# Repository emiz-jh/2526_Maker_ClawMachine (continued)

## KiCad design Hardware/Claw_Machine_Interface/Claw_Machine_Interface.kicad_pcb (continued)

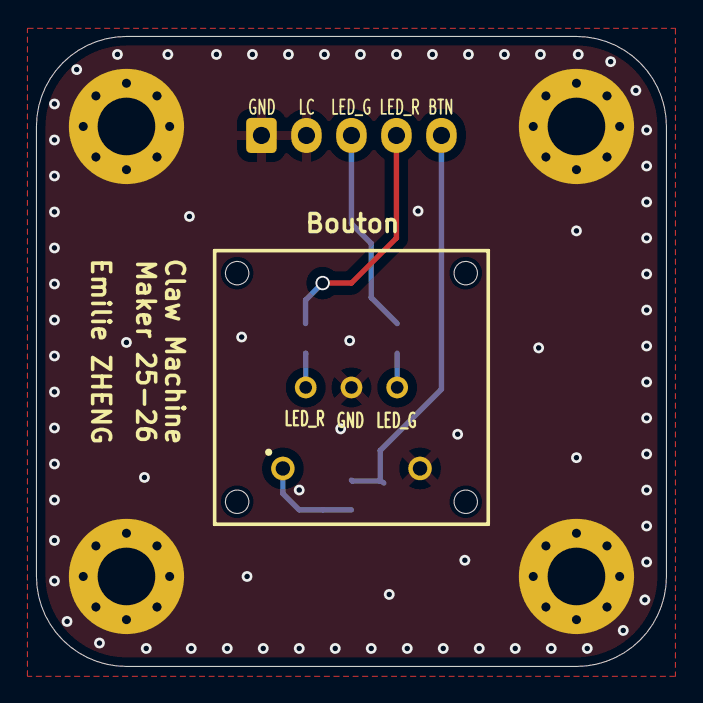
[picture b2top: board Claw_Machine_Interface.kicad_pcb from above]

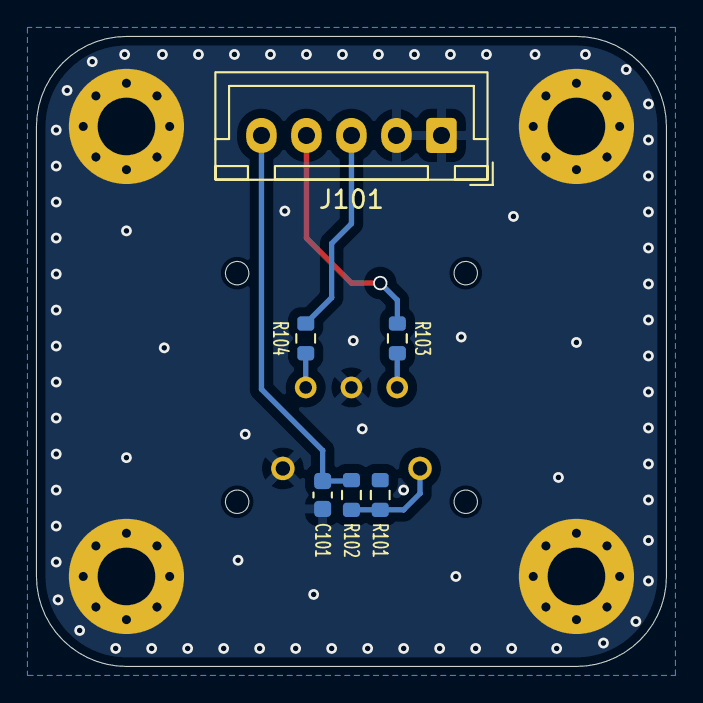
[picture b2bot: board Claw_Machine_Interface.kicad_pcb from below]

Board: 2 copper layers, 35.0 x 35.0 mm, 11 parts (6 on the bottom side), 7 nets.

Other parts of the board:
Bouton: 465RG11172501_bis

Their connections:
/LED_G: Bouton.6; also elsewhere on the board
/LED_R: Bouton.4; also elsewhere on the board
GND: Bouton.2, Bouton.5 (LC); also elsewhere on the board
unnamed 7: Bouton.1; also elsewhere on the board

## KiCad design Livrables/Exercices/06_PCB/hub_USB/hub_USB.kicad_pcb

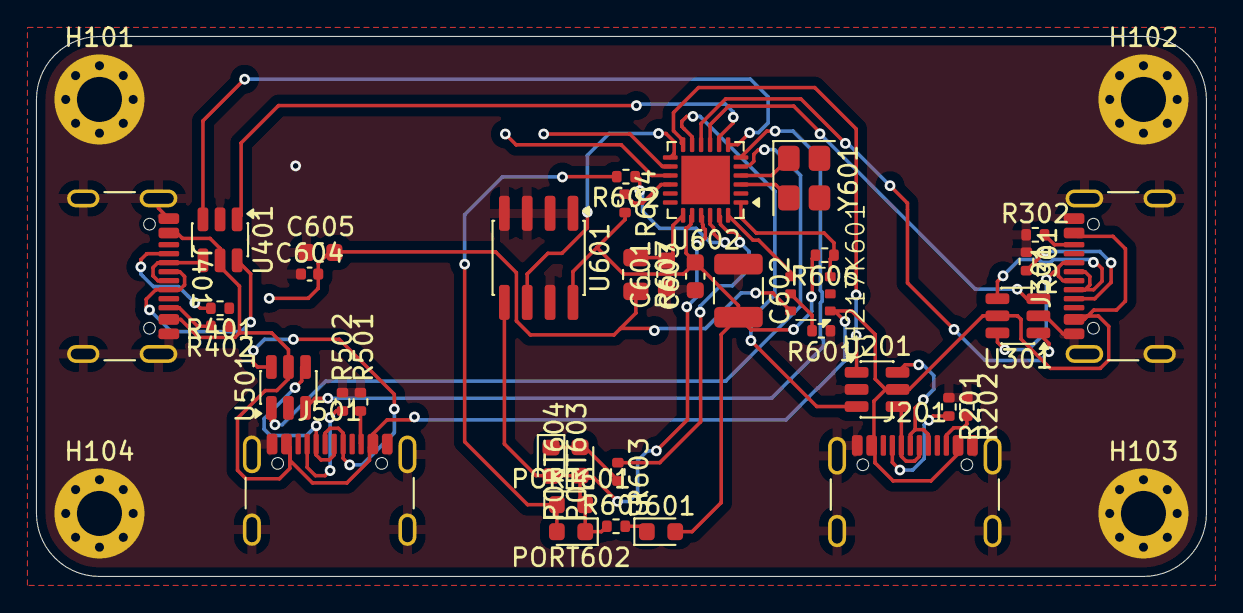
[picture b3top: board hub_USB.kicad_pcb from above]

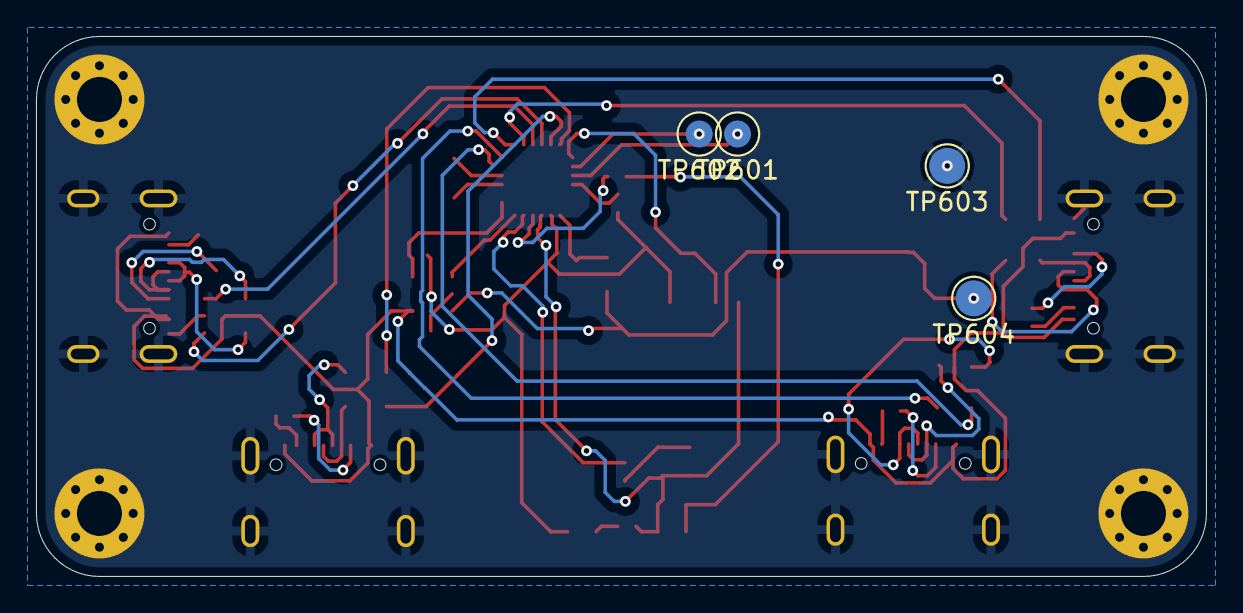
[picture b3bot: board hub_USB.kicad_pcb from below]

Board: 4 copper layers, 65.0 x 30.0 mm, 45 parts (4 on the bottom side), 44 nets.

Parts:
C601, C605: 1uF; C_0603_1608Metric
C602: 10uF; C_1210_3225Metric
C603: 0.1uF; C_0603_1608Metric
C604: 470uF; C_0402_1005Metric
CH217K601: CH217DS1
D601: ACTIVE; LED_0603_1608Metric
H101, H102, H103, H104: MountingHole_Pad; MountingHole_2.5mm_Pad_Via
J201, J301, J401, J501: USB_C_Receptacle_USB2.0_16P; USB_C_Receptacle_GCT_USB4105-xx-A_16P_TopMnt_Horizontal
PORT601, PORT602, PORT603, PORT604: RED_LED; LED_0603_1608Metric
R201, R202, R301, R302, R401, R402, R501, R502: 5.1k; R_0402_1005Metric
R601: 56K; R_0402_1005Metric
R602, R603: 220; R_0402_1005Metric
R604: NC(4K7); R_0402_1005Metric
R605: 470; R_0402_1005Metric
R606: NC(56K); R_0402_1005Metric
R607: 0; Fuse_0805_2012Metric
TP601, TP602, TP603: TestPoint; TestPoint_Pad_D2.0mm
TP604: Alim; TestPoint_Pad_D2.0mm
U201, U301, U401, U501: USBLC6-2SC6; SOT-23-6
U601: 24C02Cx-x-SN; SOIC-8_3.9x4.9mm_P1.27mm
U602: CH334F; QFN-24-1EP_4x4mm_P0.5mm_EP2.7x2.7mm
Y601: 12MHz; Crystal_SMD_3225-4Pin_3.2x2.5mm

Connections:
+3V3: C602.2, C603.2, D601.2 (A), R604.2, R606.2, U601.8 (VCC), U602.20 (VDD33_{LDO})
+5V: C604.2, C605.2, CH217K601.6 (VIN), R607.2, TP604.1
/USB1/D+: J201.A6 (D+), J201.B6 (D+), U201.6 (I/O1)
/USB1/D-: J201.A7 (D-), J201.B7 (D-), U201.4 (I/O2)
/USB1/USB_DM: U201.3 (I/O2), U602.11 (DM1-)
/USB1/USB_DP: U201.1 (I/O1), U602.12 (DP1+)
/USB1/V_USB: CH217K601.1 (VOUT), J201.A4 (VBUS), J201.A9 (VBUS), J201.B4 (VBUS), J201.B9 (VBUS), J301.A4 (VBUS), J301.A9 (VBUS), J301.B4 (VBUS), J301.B9 (VBUS), J401.A4 (VBUS), J401.A9 (VBUS), J401.B4 (VBUS), J401.B9 (VBUS), J501.A4 (VBUS), J501.A9 (VBUS), J501.B4 (VBUS), J501.B9 (VBUS), U201.5 (VBUS), U301.5 (VBUS), U401.5 (VBUS), U501.5 (VBUS)
/USB2/D+: J301.A6 (D+), J301.B6 (D+), U301.6 (I/O1)
/USB2/D-: J301.A7 (D-), J301.B7 (D-), U301.4 (I/O2)
/USB2/USB_DM: U301.3 (I/O2), U602.9 (DM2-)
/USB2/USB_DP: U301.1 (I/O1), U602.10 (DP2+)
/USB3/D+: J401.A6 (D+), J401.B6 (D+), U401.6 (I/O1)
/USB3/D-: J401.A7 (D-), J401.B7 (D-), U401.4 (I/O2)
/USB3/USB_DM: U401.3 (I/O2), U602.7 (DM3-)
/USB3/USB_DP: U401.1 (I/O1), U602.8 (DP3+)
/USB4/D+: J501.A6 (D+), J501.B6 (D+), U501.6 (I/O1)
/USB4/D-: J501.A7 (D-), J501.B7 (D-), U501.4 (I/O2)
/USB4/USB_DM: U501.3 (I/O2), U602.6 (DP4+)
/USB4/USB_DP: U501.1 (I/O1), U602.5 (DM4-)
/USB_hub_controller/OVCUR#: CH217K601.3 (FLAG#), R606.1, U602.1 (~OVCUR)
/USB_hub_controller/PLED1: R602.1, U602.22 (LED1)
/USB_hub_controller/PLED2: R603.1, U602.23 (LED2)
/USB_hub_controller/PLED3: U601.6 (SCL), U602.13 (LED3/SCL)
/USB_hub_controller/PLED4: PORT601.2 (A), PORT602.1 (K), PORT603.2 (A), PORT604.1 (K), R605.1, U601.5 (SDA), U602.21 (LED4/SDA)
/USB_hub_controller/PW REN#: CH217K601.4 (EN#), U602.24 (~PWREN)
/USB_hub_controller/RESET#: R604.1, U602.16 (~RESET/CDP)
/USB_hub_controller/XI: U602.4 (XI), Y601.1
/USB_hub_controller/XO: U602.3 (XO), Y601.2
GND: C601.1, C602.1, C603.1, C604.1, C605.1, CH217K601.2 (GND), H101.1, H102.1, H103.1, H104.1, J201.A1 (GND), J201.A12 (GND), J201.B1 (GND), J201.B12 (GND), J201.S1 (SHIELD), J301.A1 (GND), J301.A12 (GND), J301.B1 (GND), J301.B12 (GND), J301.S1 (SHIELD), J401.A1 (GND), J401.A12 (GND), J401.B1 (GND), J401.B12 (GND), J401.S1 (SHIELD), J501.A1 (GND), J501.A12 (GND), J501.B1 (GND), J501.B12 (GND), J501.S1 (SHIELD), R201.1, R202.1, R301.1, R302.1, R401.1, R402.1, R501.1, R502.1, R601.1, TP603.1, U201.2 (GND), U301.2 (GND), U401.2 (GND), U501.2 (GND), U601.1 (A0), U601.2 (A1), U601.3 (A2), U601.4 (GND), U601.7 (WP), U602.25 (GND)
unnamed: CH217K601.5 (ISET), R601.2
unnamed: D601.1 (K), R605.2
unnamed: J201.A5 (CC1), R201.2
unnamed: J201.B5 (CC2), R202.2
unnamed: J301.A5 (CC1), R301.2
unnamed: J301.B5 (CC2), R302.2
unnamed: J401.A5 (CC1), R401.2
unnamed: J401.B5 (CC2), R402.2
unnamed: J501.A5 (CC1), R501.2
unnamed: J501.B5 (CC2), R502.2
unnamed: PORT601.1 (K), PORT602.2 (A), R602.2
unnamed: PORT603.1 (K), PORT604.2 (A), R603.2
unnamed: TP602.1, U602.14 (DMU-)
unnamed: TP601.1, U602.15 (DPU+)
unnamed: C601.2, R607.1, U602.19 (V5)

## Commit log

2026-01-18 Initialisation projet
2026-01-18 Remove readme.md
2026-01-18 MAJ README et creation dossiers
2026-01-18 MAJ README
2026-01-18 MAJ Gantt et corrections liens
2026-01-18 MAJ Gantt
2026-01-28 MAJ Useless Box
2026-01-28 Ajout Maker_Exercices.md
    Added exercises for CAO, 3D printing, and laser cutting with corresponding images.
2026-05-07 Create CAD
